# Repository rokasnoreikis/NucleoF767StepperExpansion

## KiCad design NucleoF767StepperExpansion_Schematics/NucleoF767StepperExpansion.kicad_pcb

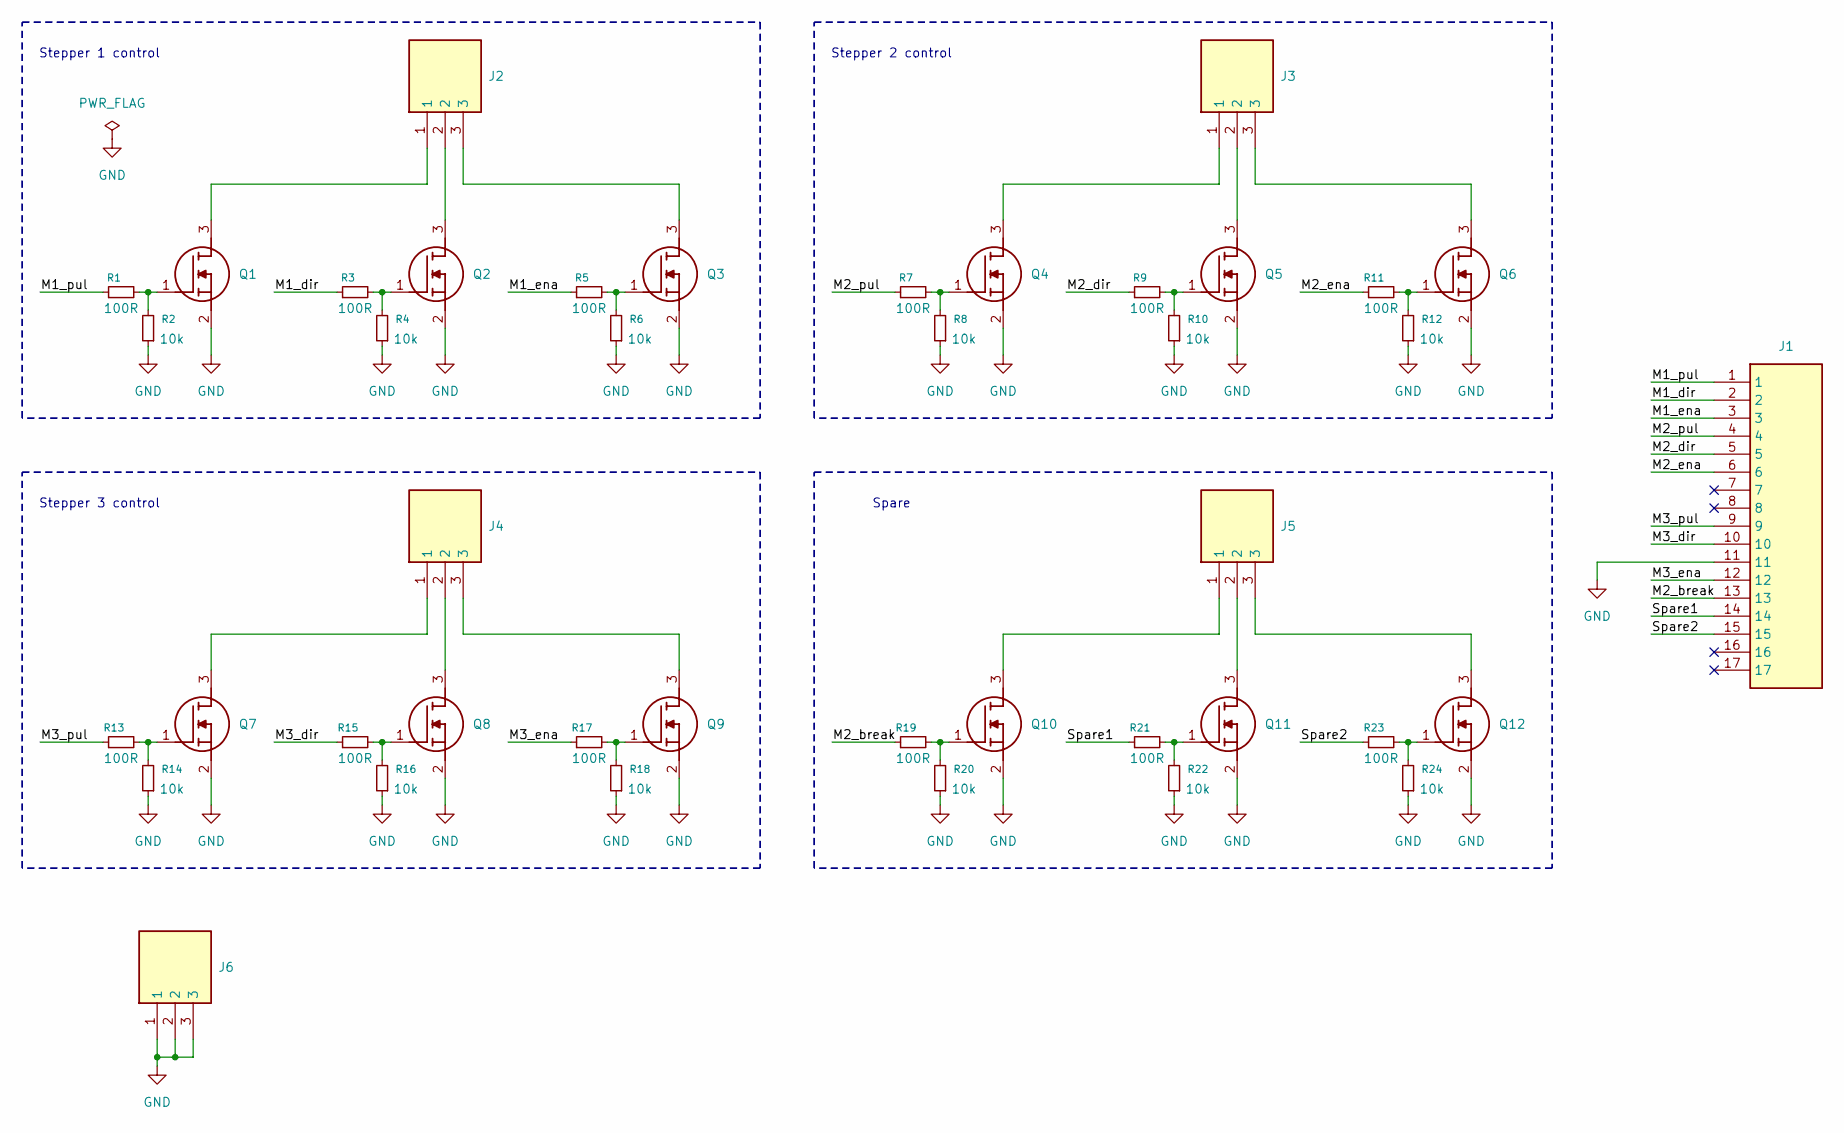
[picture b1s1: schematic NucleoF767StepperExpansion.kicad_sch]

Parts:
J1: TSW-117-07-L-S; TSW-117-XX-YY-S; Mouser Part Number 200-TSW11707LS
J2, J3, J4, J5, J6: 1715734; Mouser Part Number 651-1715734
Q1, Q2, Q3, Q4, Q5, Q6, Q7, Q8, Q9, Q10, Q11, Q12: SSM3K339R,LF; SOTFL95P240X88-3N; Mouser Part Number 757-SSM3K339RLF
R1, R3, R5, R7, R9, R11, R13, R15, R17, R19, R21, R23: 100R; R_0603_1608Metric_Pad0.98x0.95mm_HandSolder
R2, R4, R6, R8, R10, R12, R14, R16, R18, R20, R22, R24: 10k; R_0603_1608Metric_Pad0.98x0.95mm_HandSolder

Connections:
/M1_dir: J1.2, R3.1
/M1_ena: J1.3, R5.1
/M1_pul: J1.1, R1.1
/M2_break: J1.13, R19.1
/M2_dir: J1.5, R9.1
/M2_ena: J1.6, R11.1
/M2_pul: J1.4, R7.1
/M3_dir: J1.10, R15.1
/M3_ena: J1.12, R17.1
/M3_pul: J1.9, R13.1
/Spare1: J1.14, R21.1
/Spare2: J1.15, R23.1
GND: J1.11, J6.1, J6.2, J6.3, Q1.2 (S), Q2.2 (S), Q3.2 (S), Q4.2 (S), Q5.2 (S), Q6.2 (S), Q7.2 (S), Q8.2 (S), Q9.2 (S), Q10.2 (S), Q11.2 (S), Q12.2 (S), R2.1, R4.1, R6.1, R8.1, R10.1, R12.1, R14.1, R16.1, R18.1, R20.1, R22.1, R24.1
unnamed: J2.1, Q1.3 (D)
unnamed: Q1.1 (G), R1.2, R2.2
unnamed: J2.2, Q2.3 (D)
unnamed: Q2.1 (G), R3.2, R4.2
unnamed: J2.3, Q3.3 (D)
unnamed: Q3.1 (G), R5.2, R6.2
unnamed: J3.1, Q4.3 (D)
unnamed: Q4.1 (G), R7.2, R8.2
unnamed: J3.2, Q5.3 (D)
unnamed: Q5.1 (G), R9.2, R10.2
unnamed: J3.3, Q6.3 (D)
unnamed: Q6.1 (G), R11.2, R12.2
unnamed: J4.1, Q7.3 (D)
unnamed: Q7.1 (G), R13.2, R14.2
unnamed: J4.2, Q8.3 (D)
unnamed: Q8.1 (G), R15.2, R16.2
unnamed: J4.3, Q9.3 (D)
unnamed: Q9.1 (G), R17.2, R18.2
unnamed: J5.1, Q10.3 (D)
unnamed: Q10.1 (G), R19.2, R20.2
unnamed: J5.2, Q11.3 (D)
unnamed: Q11.1 (G), R21.2, R22.2
unnamed: J5.3, Q12.3 (D)
unnamed: Q12.1 (G), R23.2, R24.2

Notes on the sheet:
Stepper 3 control
Stepper 2 control
Spare
Stepper 1 control

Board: 2 copper layers, 42 parts (0 on the bottom side), 37 nets, no tracks yet.
